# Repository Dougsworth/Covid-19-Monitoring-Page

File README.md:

# Covid-19 Monitoring Project

## Description
An IEEE-funded project undertaken in response to the COVID-19 pandemic by the UWI Mona, IEEE Student Branch.

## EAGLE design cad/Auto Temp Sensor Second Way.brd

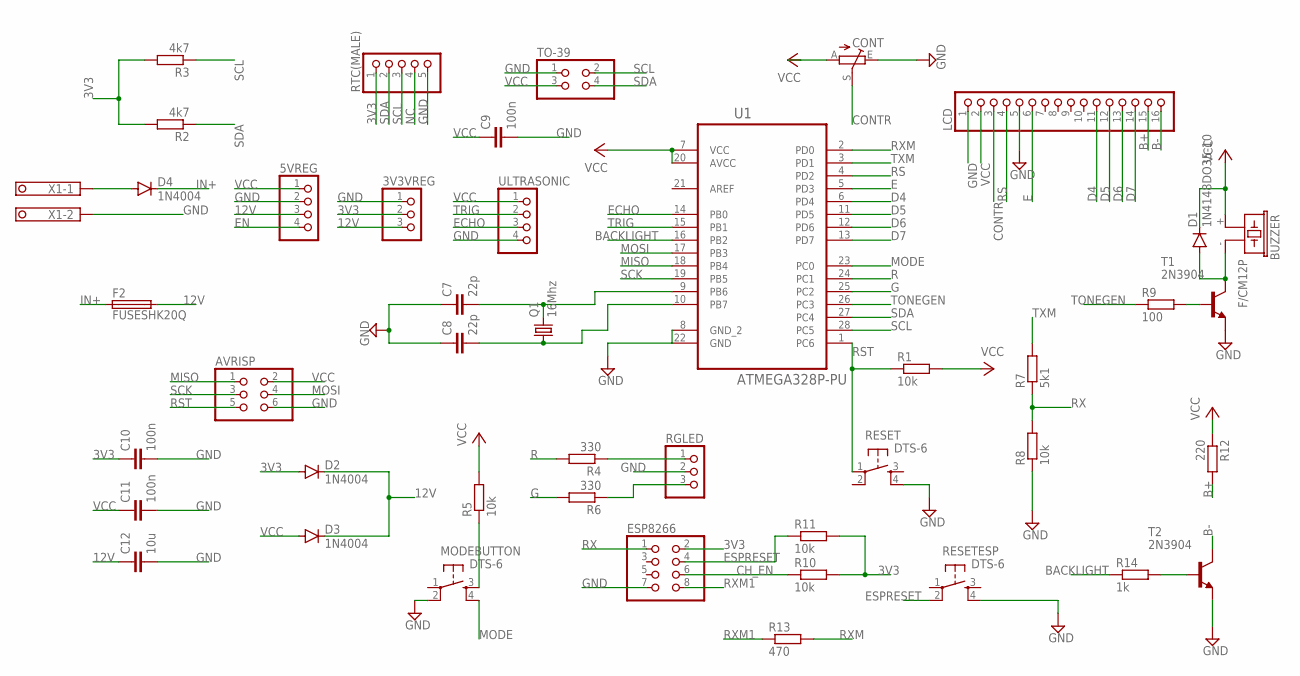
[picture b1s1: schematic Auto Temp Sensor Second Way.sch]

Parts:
3V3VREG: PINHD-1X3M; 1X03M
5VREG: PINHD-1X4M; 1X04M
AVRISP: PINHD-2X3; 2X03
BUZZER: F/CM12P
C7, C8: 22p; C050-024X044
C9, C10, C11: 100n; C050-024X044
C12: 10u; C050-024X044
CONT: 10k; B25P
D1: 1N4148DO35-10; DO35-10
D2, D3, D4: 1N4004; DO41-10
ESP8266: PINHD-2X4; 2X04
F2: FUSESHK20Q; SHK20Q
LCD: PINHD-1X16; 1X16
MODEBUTTON: DTS-6
Q1: 16Mhz; HC49/S
R1, R5, R8, R10, R11: 10k; 0207/10
R2, R3: 4k7; 0207/10
R4, R6: 330; 0207/10
R7: 5k1; 0207/10
R9: 100; 0207/10
R12: 220; 0207/10
R13: 470; 0207/10
R14: 1k; 0207/10
RESET: DTS-6
RESETESP: DTS-6
RGLED: PINHD-1X3M; 1X03M
RTC(MALE): PINHD-1X5; 1X05
T1, T2: 2N3904; TO92
TO-39: PINHD-2X2; 2X02
U1: ATMEGA328P-PU; DIP254P762X457-28
ULTRASONIC: PINHD-1X4; 1X04
X1: TERMINAL-BLOCK-3.5MM-2-PIN-LONG-PAD; TERMINAL-BLOCK-2-PIN-3.5MM-LONG-PAD

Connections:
3V3: 3V3VREG.2, C10.1, D2.A, ESP8266.2, R2.2, R3.2, R10.2, R11.2, RTC(MALE).1
12V: 3V3VREG.3, 5VREG.3, C12.1, D2.C, D3.C, F2.2A (2)
B+: LCD.15, R12.2
B-: LCD.16, T2.1 (C)
BACKLIGHT: R14.1, U1.16 (PB2)
CH_EN: ESP8266.6, R10.1
CONTR: CONT.S, LCD.3
D4: LCD.11, U1.6 (PD4)
D5: LCD.12, U1.11 (PD5)
D6: LCD.13, U1.12 (PD6)
D7: LCD.14, U1.13 (PD7)
E: LCD.6, U1.5 (PD3)
ECHO: U1.14 (PB0), ULTRASONIC.3
EN: 5VREG.4
ESPRESET: ESP8266.4, R11.1, RESETESP.2
G: R6.2, U1.25 (PC2)
GND: 3V3VREG.1, 5VREG.2, AVRISP.6, C7.1, C8.1, C9.2, C10.2, C11.2, C12.2, CONT.E, ESP8266.7, LCD.1, LCD.5, MODEBUTTON.2, R8.1, RESET.4, RESETESP.4, RGLED.2, RTC(MALE).5, T1.3 (E), T2.3 (E), TO-39.1, U1.8 (GND_2), U1.22 (GND), ULTRASONIC.4, X1.2
IN+: D4.C, F2.1A (1)
MISO: AVRISP.1, U1.18 (PB4)
MODE: MODEBUTTON.4, U1.23 (PC0)
MOSI: AVRISP.4, U1.17 (PB3)
unnamed: R14.2, T2.2 (B)
unnamed: C8.2, Q1.1, U1.10 (PB7)
unnamed: C7.2, Q1.2, U1.9 (PB6)
unnamed: D4.A, X1.1
unnamed: R4.1, RGLED.1
unnamed: R6.1, RGLED.3
unnamed: MODEBUTTON.3, R5.1
unnamed: BUZZER.- (2), D1.A, T1.1 (C)
unnamed: R9.2, T1.2 (B)
NC: RTC(MALE).4
R: R4.2, U1.24 (PC1)
RS: LCD.4, U1.4 (PD2)
RST: AVRISP.5, R1.1, RESET.1, U1.1 (PC6)
RX: ESP8266.1, R7.1, R8.2
RXM: R13.2, U1.2 (PD0)
RXM1: ESP8266.8, R13.1
SCK: AVRISP.3, U1.19 (PB5)
SCL: R3.1, RTC(MALE).3, TO-39.2, U1.28 (PC5)
SDA: R2.1, RTC(MALE).2, TO-39.4, U1.27 (PC4)
TONEGEN: R9.1, U1.26 (PC3)
TRIG: U1.15 (PB1), ULTRASONIC.2
TXM: R7.2, U1.3 (PD1)
VCC: 5VREG.1, AVRISP.2, BUZZER.+ (1), C9.1, C11.1, CONT.A, D1.C, D3.A, LCD.2, R1.2, R5.2, R12.1, TO-39.3, U1.7 (VCC), U1.20 (AVCC), ULTRASONIC.1

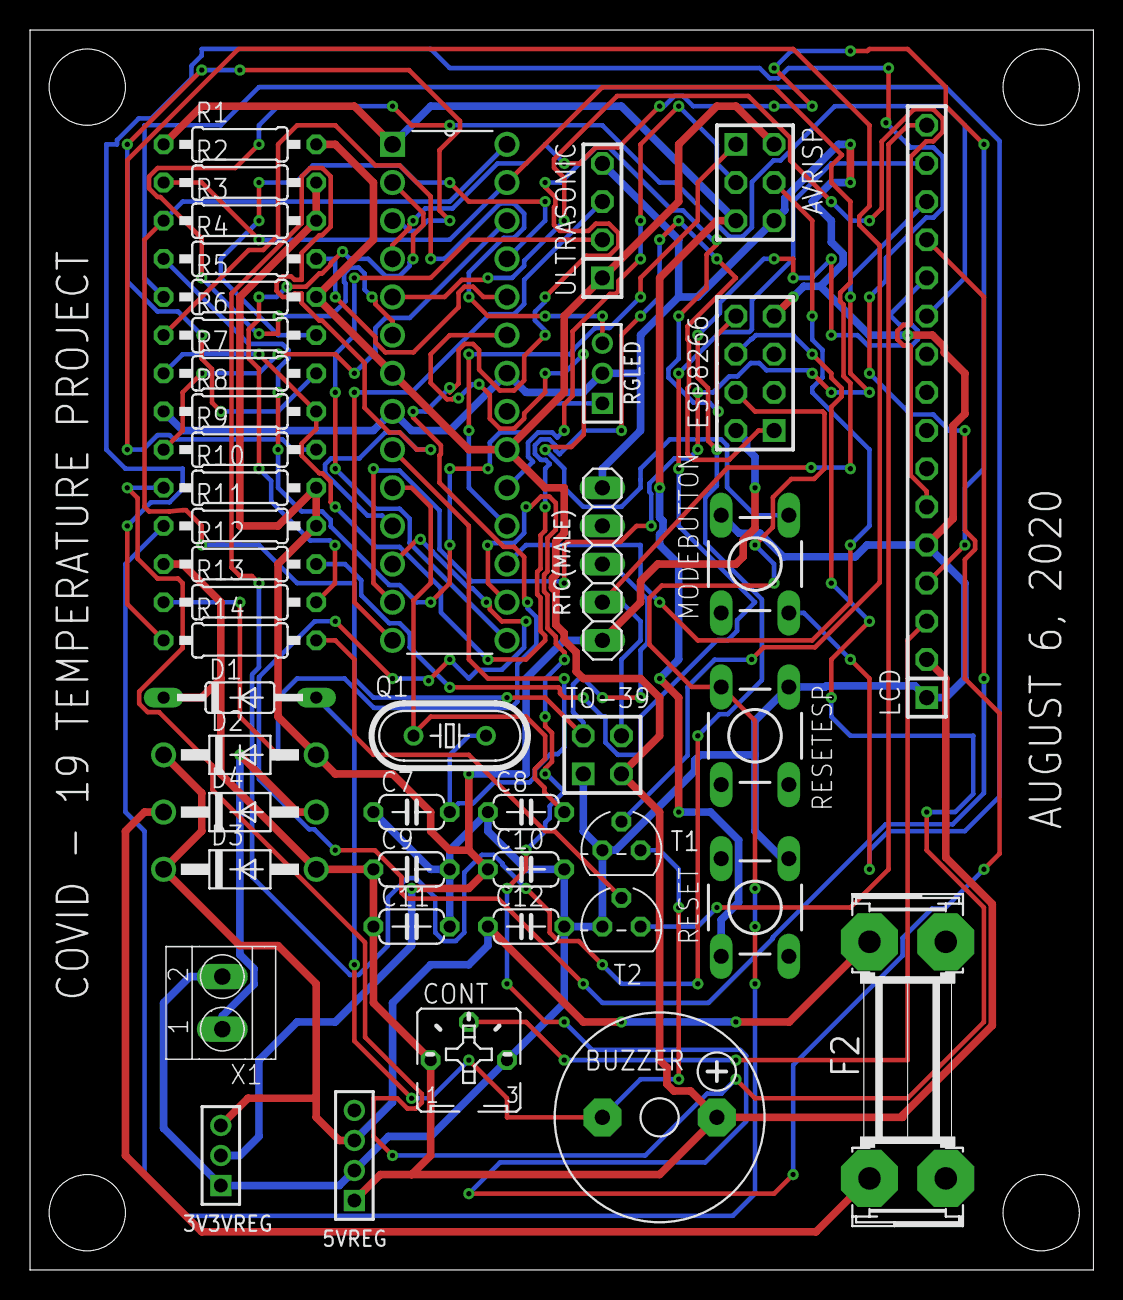
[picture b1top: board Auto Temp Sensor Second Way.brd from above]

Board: 2 copper layers, 70.8 x 82.5 mm, 44 parts (0 on the bottom side), 42 nets.

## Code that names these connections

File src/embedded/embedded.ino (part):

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//LCD
#define RS 2
#define EN 3
#define Backlight 10
LiquidCrystal lcd(RS, EN, 4, 5, 6, 7);

//RTC
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uint8_t secs;

//Ultrasonic
#define Echo 8
#define Trig 9
Ultrasonic ultrasonic(Trig, Echo);

//SD Card
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
  //LCD Setup
  lcd.begin(16, 2); 
  pinMode(Backlight, OUTPUT);
  backlightOff();

  //RTC Setup
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
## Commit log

2021-08-31 edits
2021-09-05 updating file structure
2021-09-05 Integrating SD card
2021-09-05 Generate table rows dynamically
2021-09-05 Matched IO pins to schematic
2021-09-09 Moved js to separate file
2021-09-09 Testing POST requests from embedded circuit
2021-09-09 format POST into dict
2021-09-11 Update file structure
2021-09-11 update server
2021-09-12 add login and signup
2021-09-26 fully functional
2021-10-25 Updating for additional data
